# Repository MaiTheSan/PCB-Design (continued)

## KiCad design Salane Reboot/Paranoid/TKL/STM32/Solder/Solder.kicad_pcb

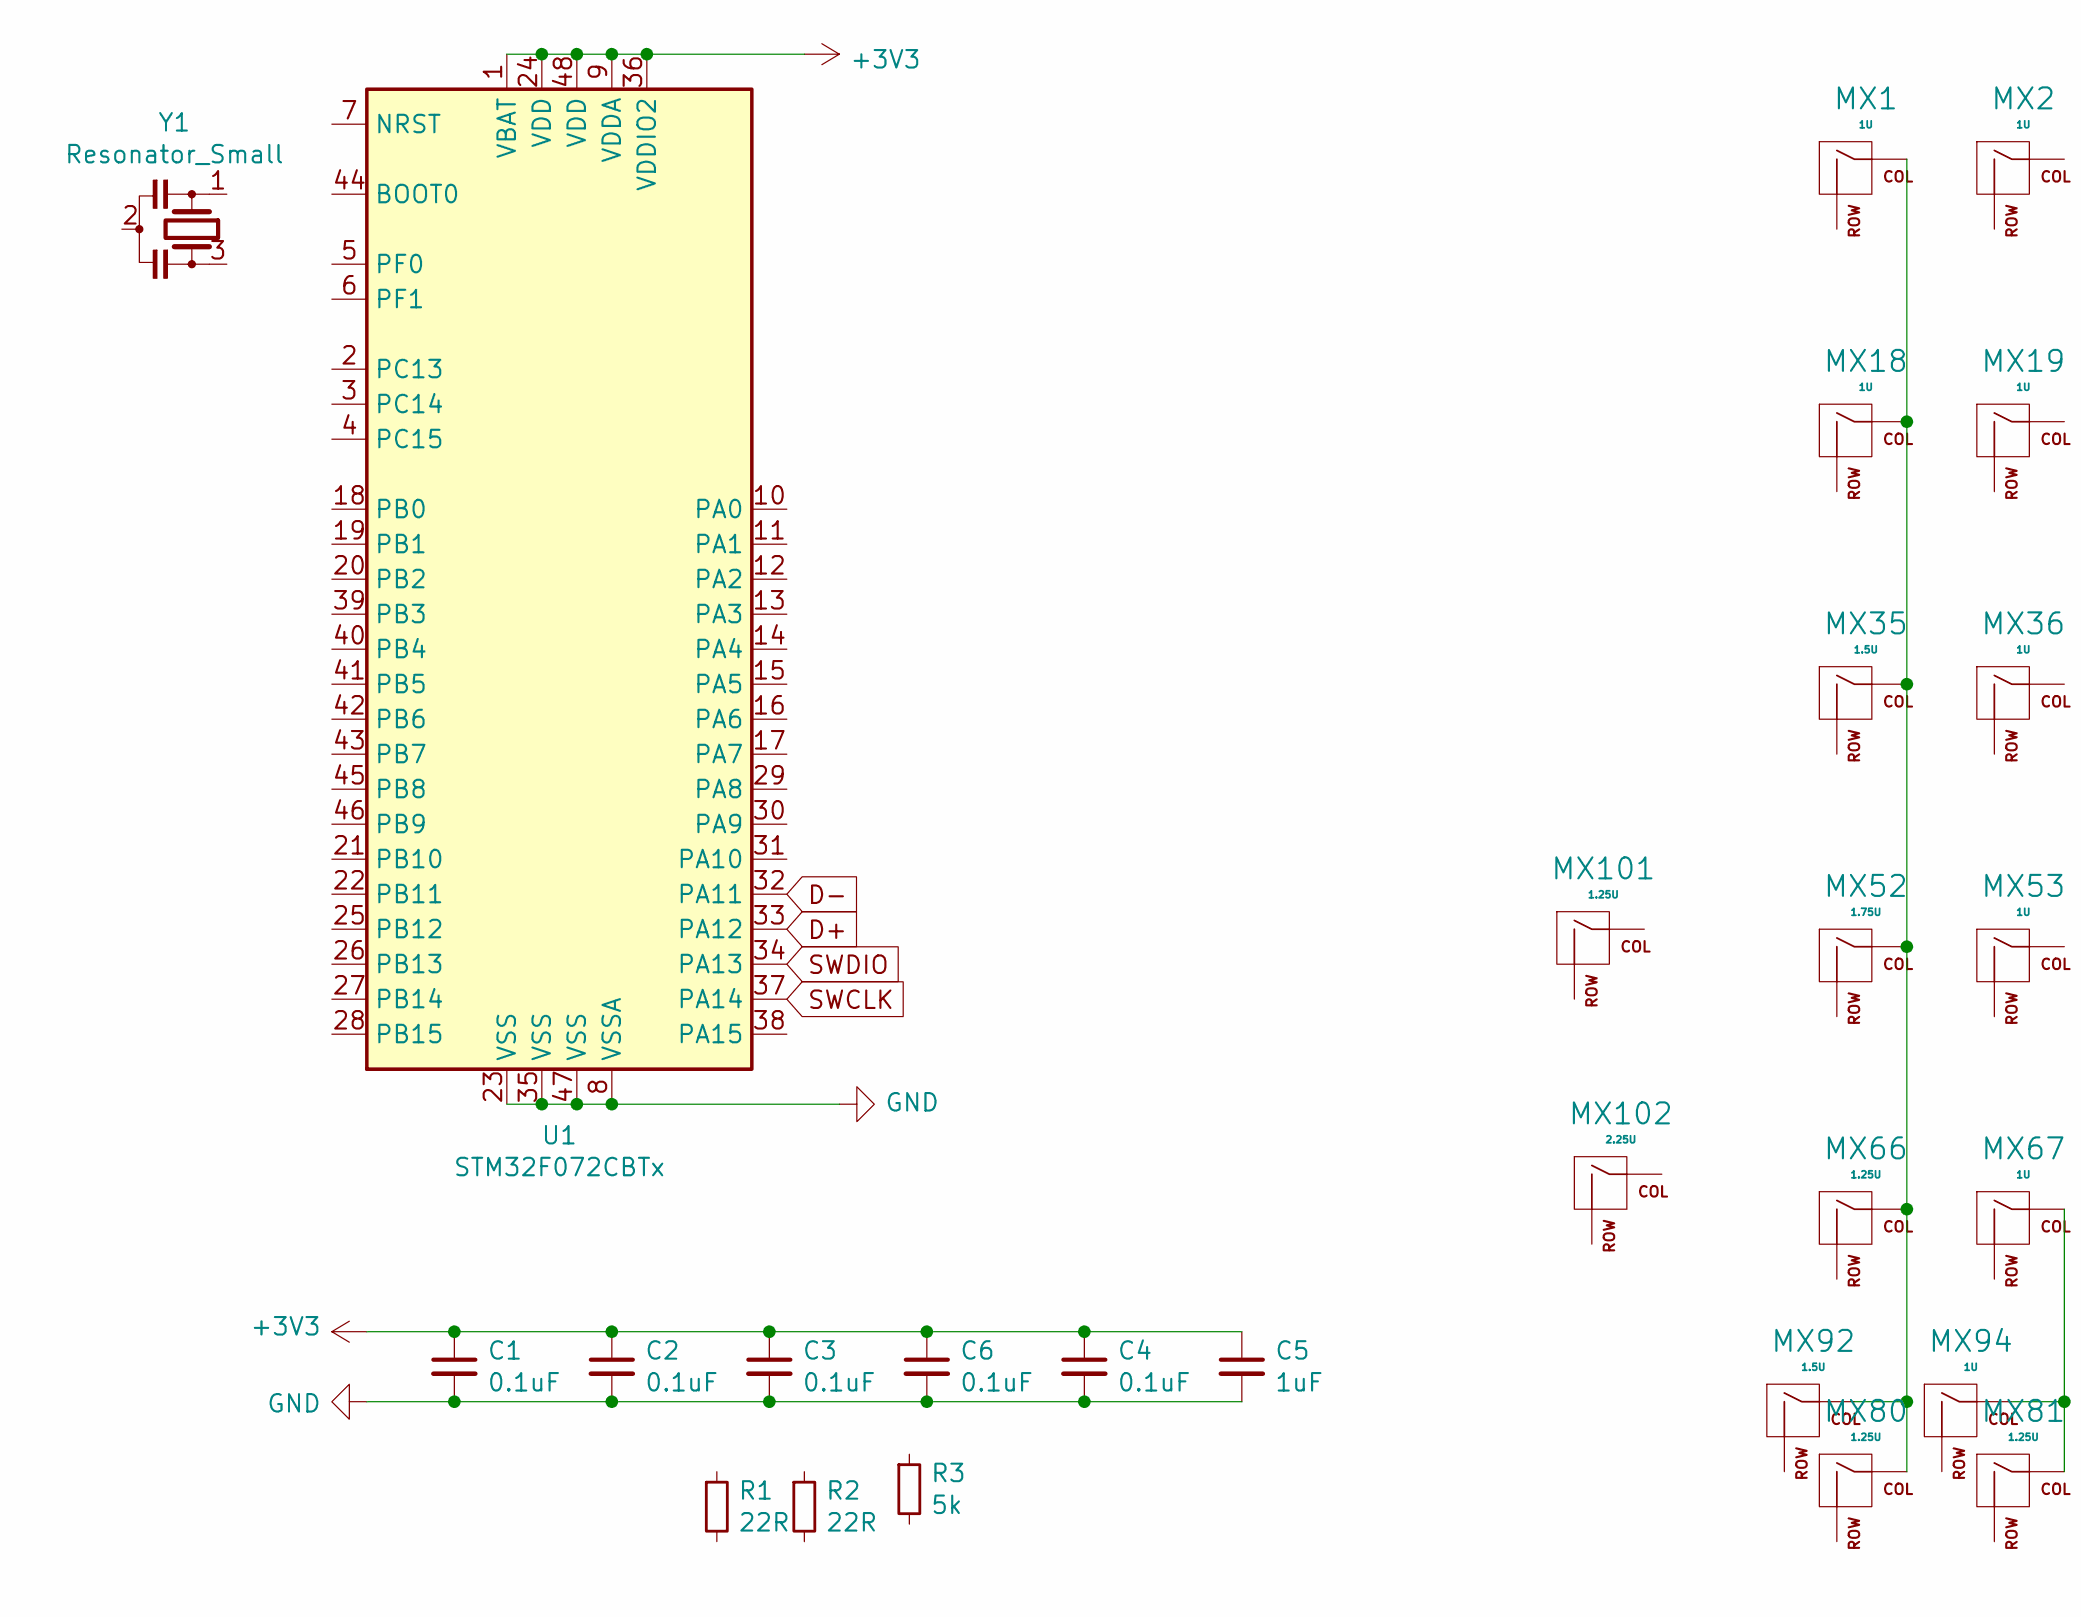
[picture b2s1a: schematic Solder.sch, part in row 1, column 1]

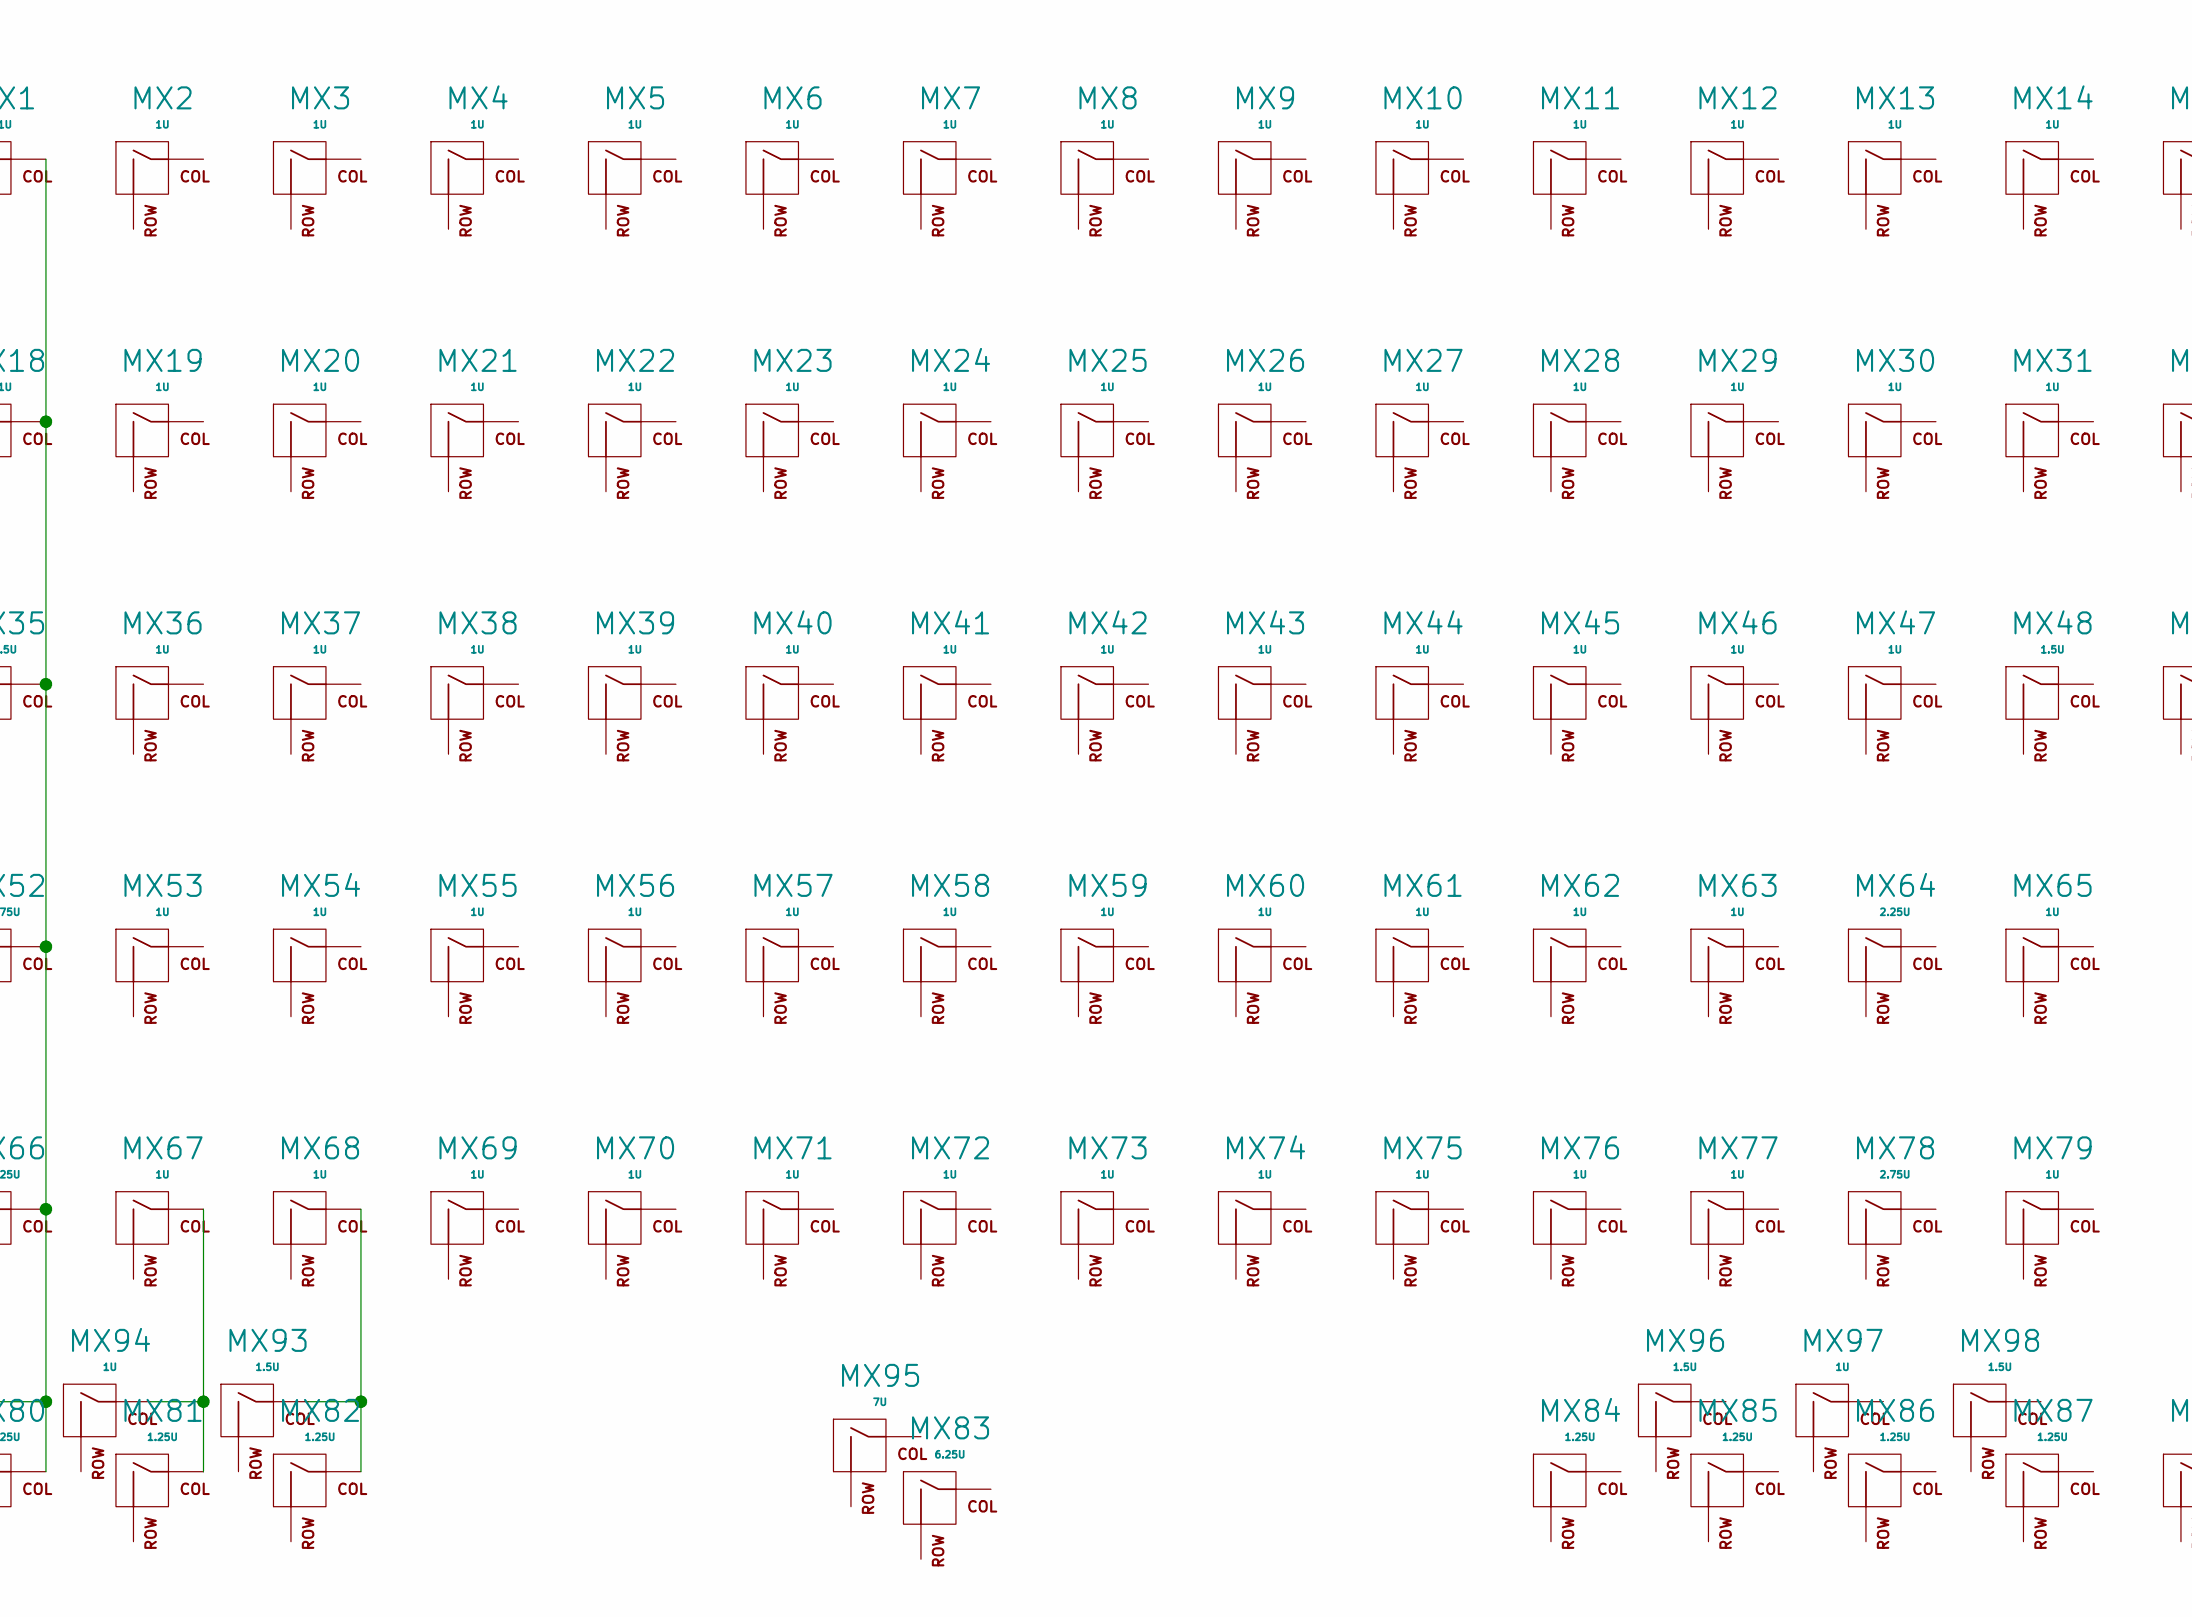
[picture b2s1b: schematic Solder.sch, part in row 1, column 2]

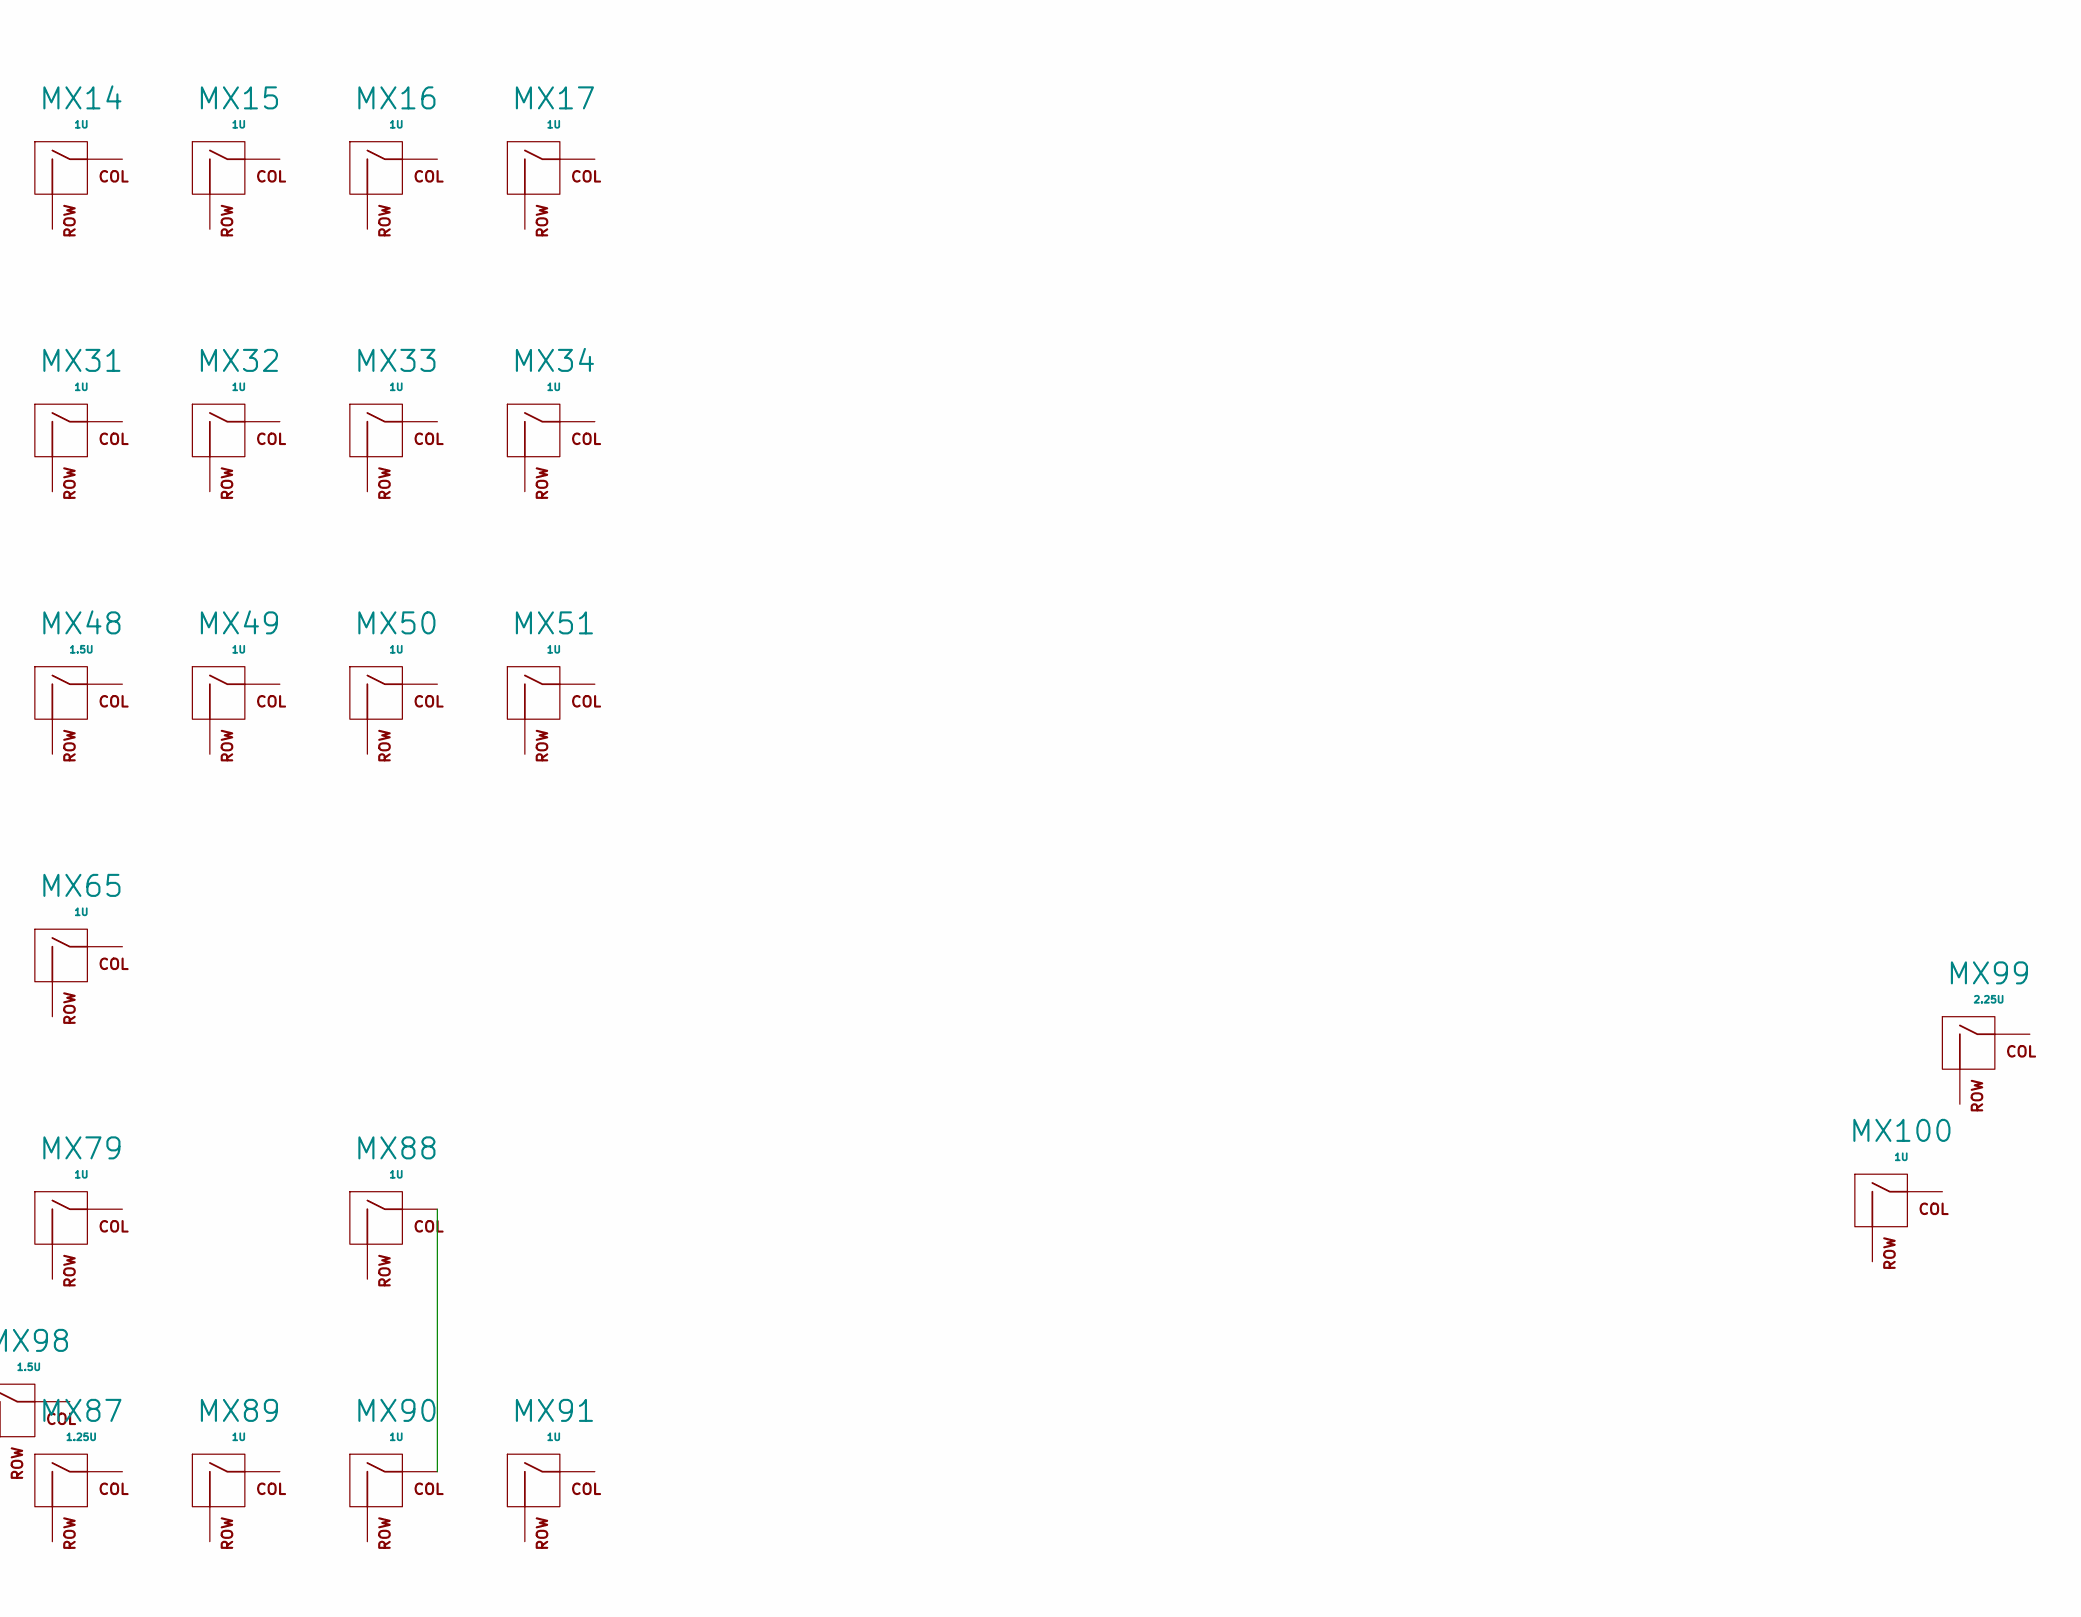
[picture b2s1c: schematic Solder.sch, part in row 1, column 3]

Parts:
C1, C2, C3, C4, C6: 0.1uF; C_0402
C5: 1uF; C_0402
MX1, MX2, MX3, MX4, MX5, MX6, MX7, MX8, MX9, MX10, MX11, MX12, MX13, MX14, MX15, MX16, MX17, MX18, MX19, MX20, MX21, MX22, MX23, MX24, MX25, MX26, MX27, MX28, MX29, MX30, MX31, MX32, MX33, MX34, MX36, MX37, MX38, MX39, MX40, MX41, MX42, MX43, MX44, MX45, MX46, MX47, MX49, MX50, MX51, MX53, MX54, MX55, MX56, MX57, MX58, MX59, MX60, MX61, MX62, MX63, MX65, MX67, MX68, MX69, MX70, MX71, MX72, MX73, MX74, MX75, MX76, MX77, MX79, MX88, MX89, MX90, MX91, MX94, MX97, MX100: 1U; MXOnly-1U-NoLED
MX35, MX48, MX92, MX93, MX96, MX98: 1.5U; MXOnly-1.5U-NoLED
MX52: 1.75U; MXOnly-1.75U-NoLED
MX64: 2.25U; MXOnly-2.25U-ReversedStabilizers-NoLED
MX66, MX80, MX81, MX82, MX84, MX85, MX86, MX87, MX101: 1.25U; MXOnly-1.25U-NoLED
MX78: 2.75U; MXOnly-2.75U-NoLED
MX83: 6.25U; MXOnly-6.25U-ReversedStabilizers-NoLED
MX95: 7U; MXOnly-7U-ReversedStabilizers-NoLED
MX99: 2.25U; MXOnly-ISO-ROTATED-ReversedStabilizers-NoLED
MX102: 2.25U; MXOnly-2.25U-NoLED
R1, R2: 22R; C_0402
R3: 5k; C_0402
U1: STM32F072CBTx; LQFP-48_7x7mm_P0.5mm
Y1: Resonator_Small; Resonator_SMD_muRata_CSTxExxV-3Pin_3.0x1.1mm

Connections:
+3V3: C1.1, C2.1, C3.1, C4.1, C5.1, C6.1, U1.1 (VBAT), U1.9 (VDDA), U1.24 (VDD), U1.36 (VDDIO2), U1.48 (VDD)
D+: U1.33 (PA12)
D-: U1.32 (PA11)
GND: C1.2, C2.2, C3.2, C4.2, C5.2, C6.2, U1.8 (VSSA), U1.23 (VSS), U1.35 (VSS), U1.47 (VSS)
unnamed: MX1.1 (COL), MX18.1 (COL), MX35.1 (COL), MX52.1 (COL), MX66.1 (COL), MX80.1 (COL), MX92.1 (COL)
unnamed: MX67.1 (COL), MX81.1 (COL), MX94.1 (COL)
unnamed: MX68.1 (COL), MX82.1 (COL), MX93.1 (COL)
unnamed: MX88.1 (COL), MX90.1 (COL)
SWCLK: U1.37 (PA14)
SWDIO: U1.34 (PA13)

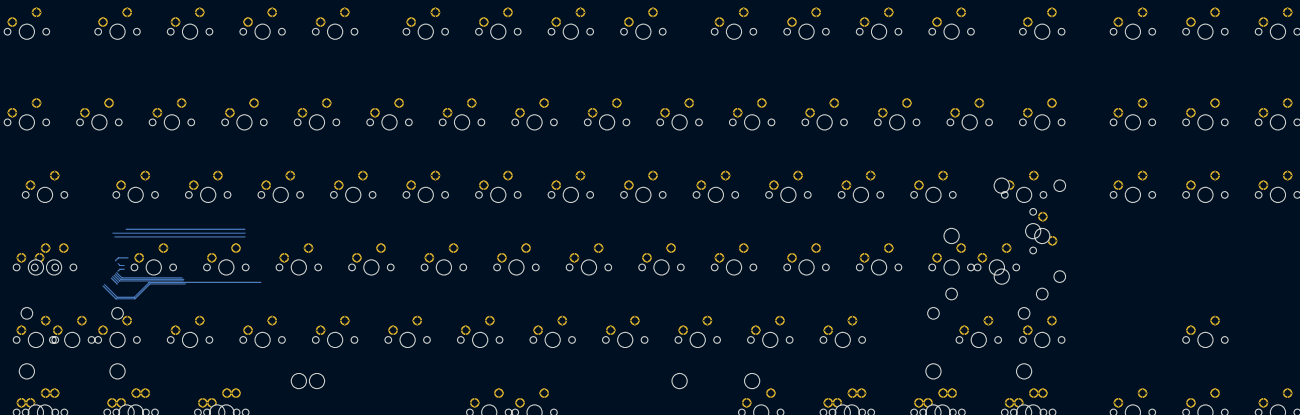
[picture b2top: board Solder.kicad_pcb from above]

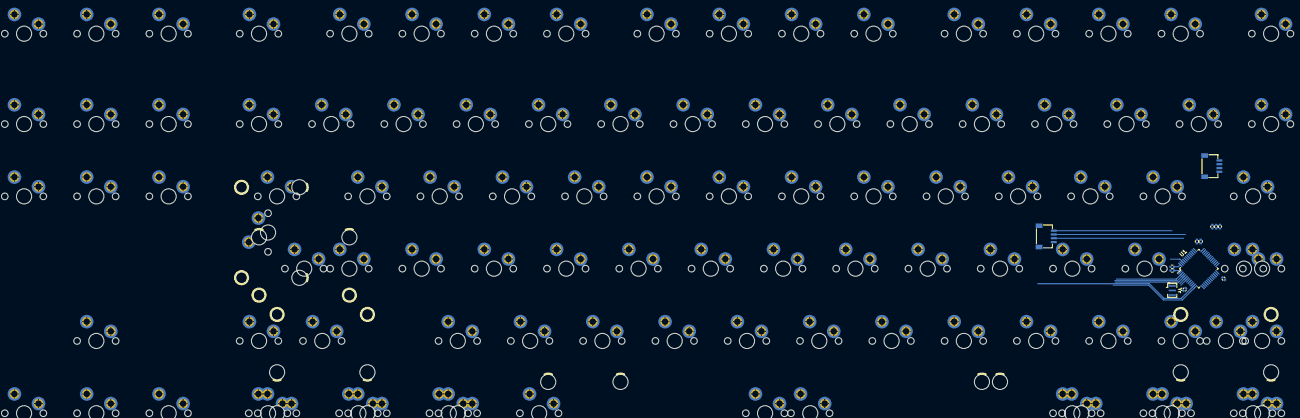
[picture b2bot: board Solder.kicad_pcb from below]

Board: 2 copper layers, 115 parts (13 on the bottom side), 6 nets.

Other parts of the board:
J1, J2: Daughterboard; JST-SR-4
Yr: Resonator_Small; Resonator_SMD_muRata_CSTxExxV-3Pin_3.0x1.1mm

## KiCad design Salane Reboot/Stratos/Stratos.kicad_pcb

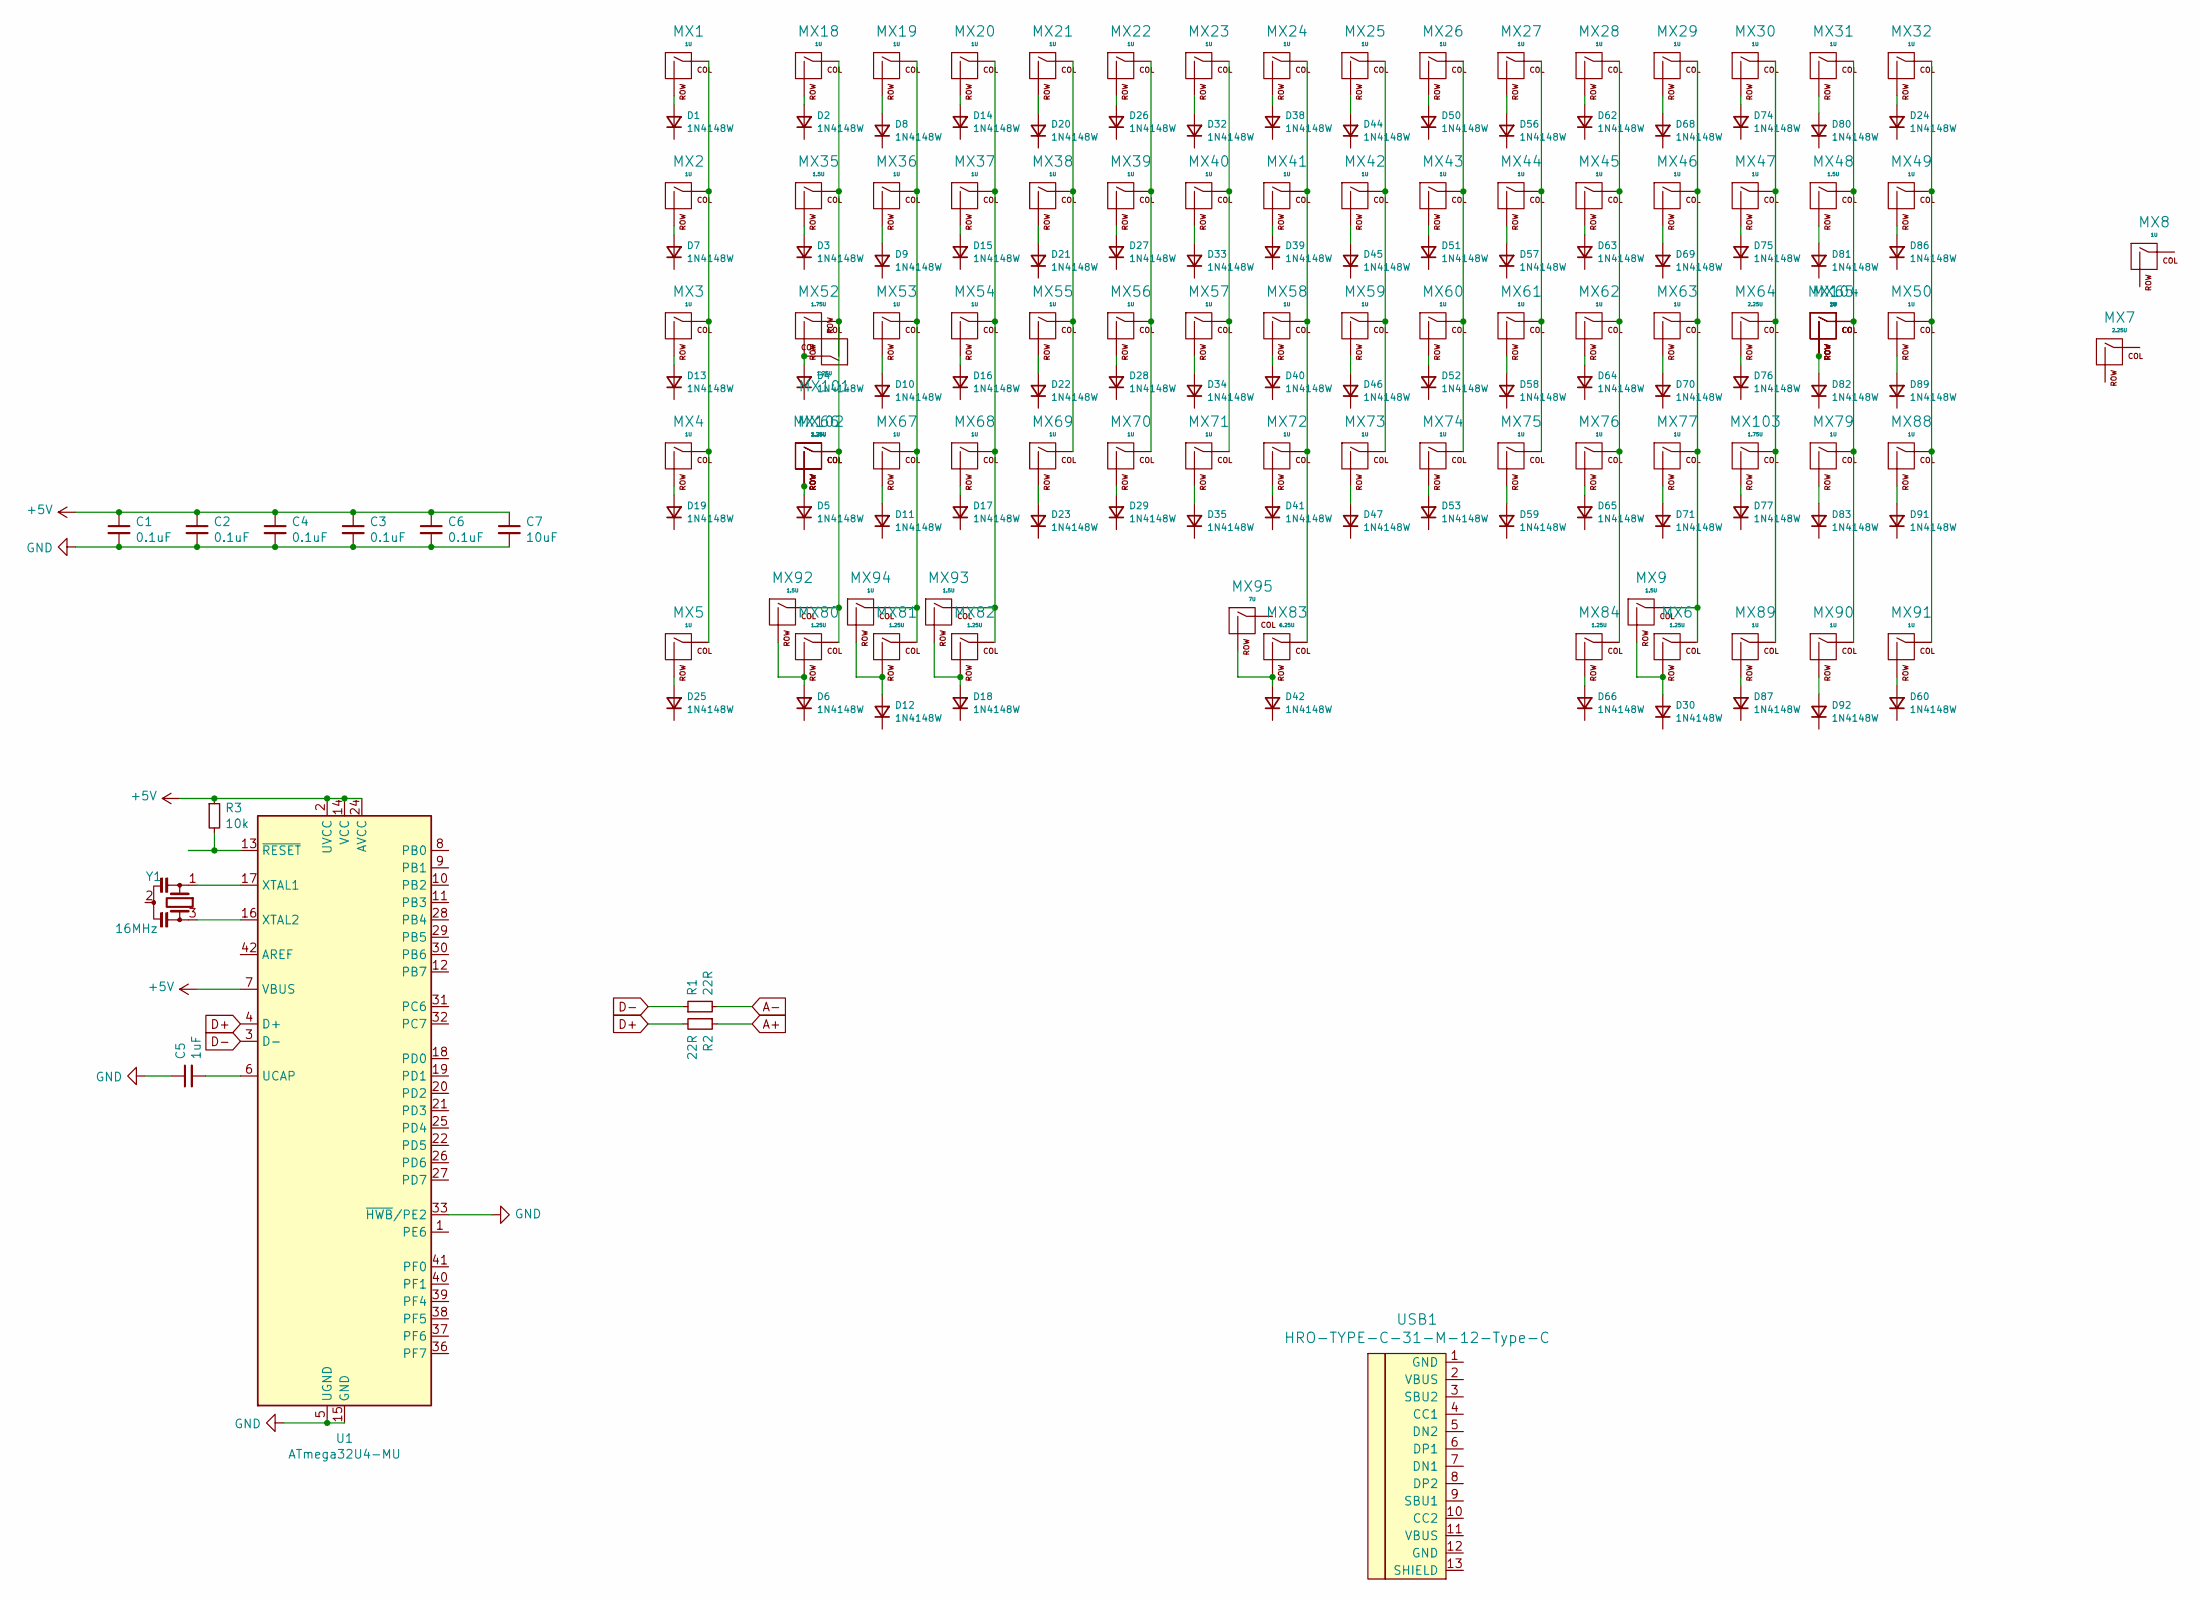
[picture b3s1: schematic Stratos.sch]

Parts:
C1, C2, C3, C4, C6: 0.1uF; C_0402
C5: 1uF; C_0402
C7: 10uF; C_0402
D1, D2, D3, D4, D5, D6, D7, D8, D9, D10, D11, D12, D13, D14, D15, D16, D17, D18, D19, D20, D21, D22, D23, D24, D25, D26, D27, D28, D29, D30, D32, D33, D34, D35, D38, D39, D40, D41, D42, D44, D45, D46, D47, D50, D51, D52, D53, D56, D57, D58, D59, D60, D62, D63, D64, D65, D66, D68, D69, D70, D71, D74, D75, D76, D77, D80, D81, D82, D83, D86, D87, D89, D91, D92: 1N4148W; DIODE_1206_SawnsProjects
MX1, MX2, MX3, MX4, MX5, MX8, MX18, MX19, MX20, MX21, MX22, MX23, MX24, MX25, MX26, MX27, MX28, MX29, MX30, MX31, MX32, MX36, MX37, MX38, MX39, MX40, MX41, MX42, MX43, MX44, MX45, MX46, MX47, MX49, MX50, MX53, MX54, MX55, MX56, MX57, MX58, MX59, MX60, MX61, MX62, MX63, MX65, MX67, MX68, MX69, MX70, MX71, MX72, MX73, MX74, MX75, MX76, MX77, MX79, MX88, MX89, MX90, MX91, MX94: 1U; MXOnly-1U-NoLED
MX6, MX66, MX80, MX81, MX82, MX84, MX101: 1.25U; MXOnly-1.25U-NoLED
MX7: 2.25U; MXOnly-ISO-ROTATED-ReversedStabilizers-NoLED
MX9, MX35, MX48, MX92, MX93: 1.5U; MXOnly-1.5U-NoLED
MX52, MX103: 1.75U; MXOnly-1.75U-NoLED
MX64: 2.25U; MXOnly-2.25U-ReversedStabilizers-NoLED
MX83: 6.25U; MXOnly-6.25U-ReversedStabilizers-NoLED
MX95: 7U; MXOnly-7U-ReversedStabilizers-NoLED
MX102: 2.25U; MXOnly-2.25U-NoLED
MX104: 2U; MXOnly-2U-NoLED
R1, R2: 22R; R_0402
R3: 10k; R_0402
U1: ATmega32U4-MU; QFN-44-1EP_7x7mm_P0.5mm_EP5.2x5.2mm
USB1: HRO-TYPE-C-31-M-12-Type-C; HRO-TYPE-C-31-M-12-Assembly
Y1: 16MHz; Resonator_SMD_muRata_CSTxExxV-3Pin_3.0x1.1mm

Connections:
+5V: C1.1, C2.1, C3.1, C4.1, C6.1, C7.1, R3.1, U1.2 (UVCC), U1.7 (VBUS), U1.14 (VCC), U1.24 (AVCC), U1.34 (VCC), U1.44 (AVCC)
A+: R2.1
A-: R1.2
D+: R2.2, U1.4 (D+)
D-: R1.1, U1.3 (D-)
GND: C1.2, C2.2, C3.2, C4.2, C5.1, C6.2, C7.2, U1.5 (UGND), U1.15 (GND), U1.23 (GND), U1.33 (~HWB~/PE2), U1.35 (GND), U1.43 (GND), U1.45 (GND)
unnamed: C5.2, U1.6 (UCAP)
unnamed: D1.2 (A), MX1.2 (ROW)
unnamed: D2.2 (A), MX18.2 (ROW)
unnamed: D3.2 (A), MX35.2 (ROW)
unnamed: D4.2 (A), MX52.2 (ROW), MX101.1 (COL)
unnamed: D5.2 (A), MX66.2 (ROW), MX102.2 (ROW)
unnamed: D6.2 (A), MX80.2 (ROW), MX92.2 (ROW)
unnamed: D7.2 (A), MX2.2 (ROW)
unnamed: D8.2 (A), MX19.2 (ROW)
unnamed: D9.2 (A), MX36.2 (ROW)
unnamed: D10.2 (A), MX53.2 (ROW)
unnamed: D11.2 (A), MX67.2 (ROW)
unnamed: D12.2 (A), MX81.2 (ROW), MX94.2 (ROW)
unnamed: D13.2 (A), MX3.2 (ROW)
unnamed: D14.2 (A), MX20.2 (ROW)
unnamed: D15.2 (A), MX37.2 (ROW)
unnamed: D16.2 (A), MX54.2 (ROW)
unnamed: D17.2 (A), MX68.2 (ROW)
unnamed: D18.2 (A), MX82.2 (ROW), MX93.2 (ROW)
unnamed: D19.2 (A), MX4.2 (ROW)
unnamed: D20.2 (A), MX21.2 (ROW)
unnamed: D21.2 (A), MX38.2 (ROW)
unnamed: D22.2 (A), MX55.2 (ROW)
unnamed: D23.2 (A), MX69.2 (ROW)
unnamed: D24.2 (A), MX32.2 (ROW)
unnamed: D25.2 (A), MX5.2 (ROW)
unnamed: D26.2 (A), MX22.2 (ROW)
unnamed: D27.2 (A), MX39.2 (ROW)
unnamed: D28.2 (A), MX56.2 (ROW)
unnamed: D29.2 (A), MX70.2 (ROW)
unnamed: D30.2 (A), MX6.2 (ROW), MX9.2 (ROW)
unnamed: D32.2 (A), MX23.2 (ROW)
unnamed: D33.2 (A), MX40.2 (ROW)
unnamed: D34.2 (A), MX57.2 (ROW)
unnamed: D35.2 (A), MX71.2 (ROW)
unnamed: D38.2 (A), MX24.2 (ROW)
unnamed: D39.2 (A), MX41.2 (ROW)
unnamed: D40.2 (A), MX58.2 (ROW)
unnamed: D41.2 (A), MX72.2 (ROW)
unnamed: D42.2 (A), MX83.2 (ROW), MX95.2 (ROW)
unnamed: D44.2 (A), MX25.2 (ROW)
unnamed: D45.2 (A), MX42.2 (ROW)
unnamed: D46.2 (A), MX59.2 (ROW)
unnamed: D47.2 (A), MX73.2 (ROW)
unnamed: D50.2 (A), MX26.2 (ROW)
unnamed: D51.2 (A), MX43.2 (ROW)
unnamed: D52.2 (A), MX60.2 (ROW)
unnamed: D53.2 (A), MX74.2 (ROW)
unnamed: D56.2 (A), MX27.2 (ROW)
unnamed: D57.2 (A), MX44.2 (ROW)
unnamed: D58.2 (A), MX61.2 (ROW)
unnamed: D59.2 (A), MX75.2 (ROW)
unnamed: D60.2 (A), MX91.2 (ROW)
unnamed: D62.2 (A), MX28.2 (ROW)
unnamed: D63.2 (A), MX45.2 (ROW)
unnamed: D64.2 (A), MX62.2 (ROW)
unnamed: D65.2 (A), MX76.2 (ROW)
unnamed: D66.2 (A), MX84.2 (ROW)
unnamed: D68.2 (A), MX29.2 (ROW)
unnamed: D69.2 (A), MX46.2 (ROW)
unnamed: D70.2 (A), MX63.2 (ROW)
unnamed: D71.2 (A), MX77.2 (ROW)
unnamed: D74.2 (A), MX30.2 (ROW)
unnamed: D75.2 (A), MX47.2 (ROW)
unnamed: D76.2 (A), MX64.2 (ROW)
unnamed: D77.2 (A), MX103.2 (ROW)
unnamed: D80.2 (A), MX31.2 (ROW)
unnamed: D81.2 (A), MX48.2 (ROW)
unnamed: D82.2 (A), MX65.2 (ROW), MX104.2 (ROW)
unnamed: D83.2 (A), MX79.2 (ROW)
unnamed: D86.2 (A), MX49.2 (ROW)
unnamed: D87.2 (A), MX89.2 (ROW)
unnamed: D89.2 (A), MX50.2 (ROW)
unnamed: D91.2 (A), MX88.2 (ROW)
unnamed: D92.2 (A), MX90.2 (ROW)
unnamed: MX1.1 (COL), MX2.1 (COL), MX3.1 (COL), MX4.1 (COL), MX5.1 (COL)
unnamed: MX19.1 (COL), MX36.1 (COL), MX53.1 (COL), MX67.1 (COL), MX81.1 (COL), MX94.1 (COL)
unnamed: MX20.1 (COL), MX37.1 (COL), MX54.1 (COL), MX68.1 (COL), MX82.1 (COL), MX93.1 (COL)
unnamed: MX21.1 (COL), MX38.1 (COL), MX55.1 (COL), MX69.1 (COL)
unnamed: MX22.1 (COL), MX39.1 (COL), MX56.1 (COL), MX70.1 (COL)
unnamed: MX23.1 (COL), MX40.1 (COL), MX57.1 (COL), MX71.1 (COL)
unnamed: MX24.1 (COL), MX41.1 (COL), MX58.1 (COL), MX72.1 (COL), MX83.1 (COL)
unnamed: MX25.1 (COL), MX42.1 (COL), MX59.1 (COL), MX73.1 (COL)
unnamed: MX26.1 (COL), MX43.1 (COL), MX60.1 (COL), MX74.1 (COL)
unnamed: MX27.1 (COL), MX44.1 (COL), MX61.1 (COL), MX75.1 (COL)
unnamed: MX28.1 (COL), MX45.1 (COL), MX62.1 (COL), MX76.1 (COL), MX84.1 (COL)
unnamed: MX6.1 (COL), MX9.1 (COL), MX29.1 (COL), MX46.1 (COL), MX63.1 (COL), MX77.1 (COL)
unnamed: MX32.1 (COL), MX49.1 (COL), MX50.1 (COL), MX88.1 (COL), MX91.1 (COL)
unnamed: MX18.1 (COL), MX35.1 (COL), MX52.1 (COL), MX66.1 (COL), MX80.1 (COL), MX92.1 (COL), MX101.2 (ROW), MX102.1 (COL)
unnamed: MX30.1 (COL), MX47.1 (COL), MX64.1 (COL), MX89.1 (COL), MX103.1 (COL)
unnamed: MX31.1 (COL), MX48.1 (COL), MX65.1 (COL), MX79.1 (COL), MX90.1 (COL), MX104.1 (COL)
unnamed: R3.2, U1.13 (~RESET)
unnamed: U1.16 (XTAL2), Y1.3
unnamed: U1.17 (XTAL1), Y1.1

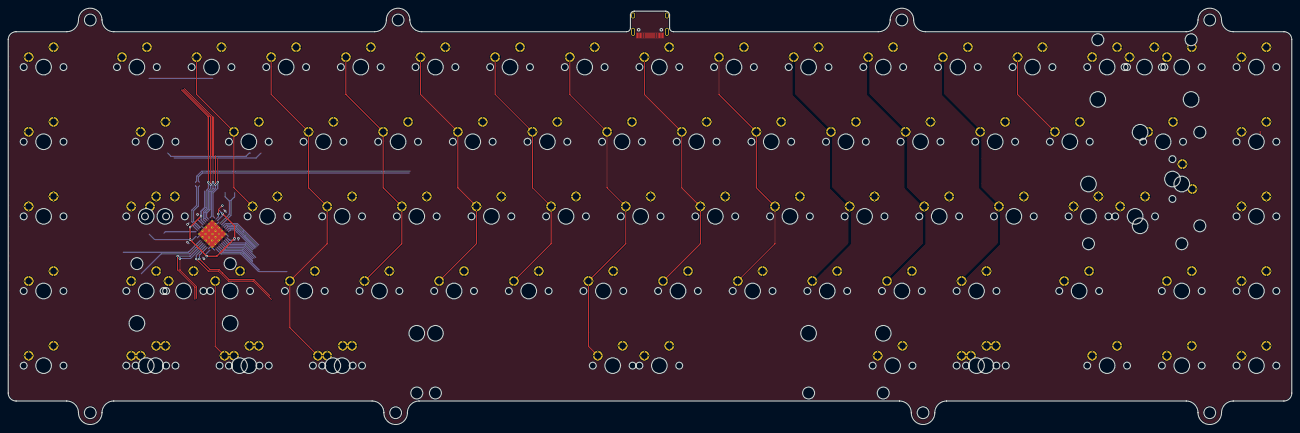
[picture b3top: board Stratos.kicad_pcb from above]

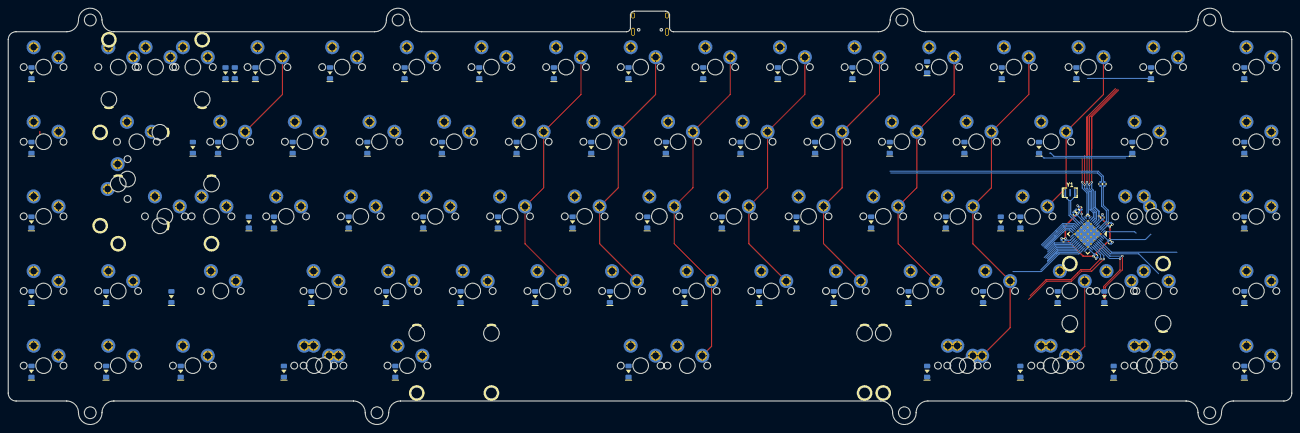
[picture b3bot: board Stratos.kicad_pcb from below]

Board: 2 copper layers, 327.6 x 106.2 mm, 171 parts (86 on the bottom side), 98 nets.
